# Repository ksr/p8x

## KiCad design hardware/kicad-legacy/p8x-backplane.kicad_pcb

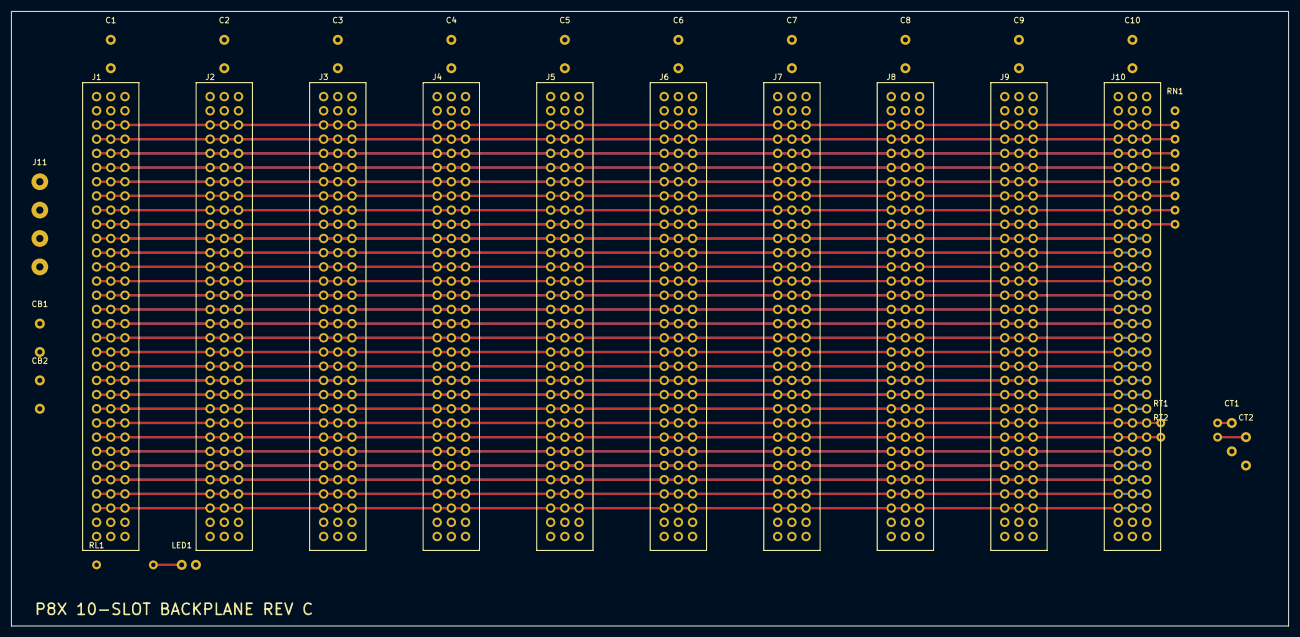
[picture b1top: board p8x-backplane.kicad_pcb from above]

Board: 4 copper layers, 228.6 x 110.0 mm, 30 parts (0 on the bottom side), 61 nets.

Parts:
C1, C2, C3, C4, C5, C6, C7, C8, C9, C10: C_DISC
CB1, CB2: CP_RADIAL
CT1, CT2: C_DISC
J1, J2, J3, J4, J5, J6, J7, J8, J9, J10: DIN96F
J11: TB4
LED1: LED5MM
RL1: R_AXIAL
RN1: SIP9
RT1, RT2: R_AXIAL

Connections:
A0: J1.C3, J2.C3, J3.C3, J4.C3, J5.C3, J6.C3, J7.C3, J8.C3, J9.C3, J10.C3
A1: J1.C4, J2.C4, J3.C4, J4.C4, J5.C4, J6.C4, J7.C4, J8.C4, J9.C4, J10.C4
A2: J1.C5, J2.C5, J3.C5, J4.C5, J5.C5, J6.C5, J7.C5, J8.C5, J9.C5, J10.C5
A3: J1.C6, J2.C6, J3.C6, J4.C6, J5.C6, J6.C6, J7.C6, J8.C6, J9.C6, J10.C6
A4: J1.C7, J2.C7, J3.C7, J4.C7, J5.C7, J6.C7, J7.C7, J8.C7, J9.C7, J10.C7
A5: J1.C8, J2.C8, J3.C8, J4.C8, J5.C8, J6.C8, J7.C8, J8.C8, J9.C8, J10.C8
A6: J1.C9, J2.C9, J3.C9, J4.C9, J5.C9, J6.C9, J7.C9, J8.C9, J9.C9, J10.C9
A7: J1.C10, J2.C10, J3.C10, J4.C10, J5.C10, J6.C10, J7.C10, J8.C10, J9.C10, J10.C10
A8: J1.C11, J2.C11, J3.C11, J4.C11, J5.C11, J6.C11, J7.C11, J8.C11, J9.C11, J10.C11
A9: J1.C12, J2.C12, J3.C12, J4.C12, J5.C12, J6.C12, J7.C12, J8.C12, J9.C12, J10.C12
A10: J1.C13, J2.C13, J3.C13, J4.C13, J5.C13, J6.C13, J7.C13, J8.C13, J9.C13, J10.C13
A11: J1.C14, J2.C14, J3.C14, J4.C14, J5.C14, J6.C14, J7.C14, J8.C14, J9.C14, J10.C14
A12: J1.C15, J2.C15, J3.C15, J4.C15, J5.C15, J6.C15, J7.C15, J8.C15, J9.C15, J10.C15
A13: J1.C16, J2.C16, J3.C16, J4.C16, J5.C16, J6.C16, J7.C16, J8.C16, J9.C16, J10.C16
A14: J1.C17, J2.C17, J3.C17, J4.C17, J5.C17, J6.C17, J7.C17, J8.C17, J9.C17, J10.C17
A15: J1.C18, J2.C18, J3.C18, J4.C18, J5.C18, J6.C18, J7.C18, J8.C18, J9.C18, J10.C18
ALUM: J1.C23, J2.C23, J3.C23, J4.C23, J5.C23, J6.C23, J7.C23, J8.C23, J9.C23, J10.C23
ALUS0: J1.C19, J2.C19, J3.C19, J4.C19, J5.C19, J6.C19, J7.C19, J8.C19, J9.C19, J10.C19
ALUS1: J1.C20, J2.C20, J3.C20, J4.C20, J5.C20, J6.C20, J7.C20, J8.C20, J9.C20, J10.C20
ALUS2: J1.C21, J2.C21, J3.C21, J4.C21, J5.C21, J6.C21, J7.C21, J8.C21, J9.C21, J10.C21
ALUS3: J1.C22, J2.C22, J3.C22, J4.C22, J5.C22, J6.C22, J7.C22, J8.C22, J9.C22, J10.C22
CIN: J1.C24, J2.C24, J3.C24, J4.C24, J5.C24, J6.C24, J7.C24, J8.C24, J9.C24, J10.C24
CLK: J1.A24, J2.A24, J3.A24, J4.A24, J5.A24, J6.A24, J7.A24, J8.A24, J9.A24, J10.A24, RT1.1
CLKB: J1.A25, J2.A25, J3.A25, J4.A25, J5.A25, J6.A25, J7.A25, J8.A25, J9.A25, J10.A25, RT2.1
CLKB_T: CT2.1, RT2.2
CLK_T: CT1.1, RT1.2
D0: J1.A3, J2.A3, J3.A3, J4.A3, J5.A3, J6.A3, J7.A3, J8.A3, J9.A3, J10.A3, RN1.2
D1: J1.A4, J2.A4, J3.A4, J4.A4, J5.A4, J6.A4, J7.A4, J8.A4, J9.A4, J10.A4, RN1.3
D2: J1.A5, J2.A5, J3.A5, J4.A5, J5.A5, J6.A5, J7.A5, J8.A5, J9.A5, J10.A5, RN1.4
D3: J1.A6, J2.A6, J3.A6, J4.A6, J5.A6, J6.A6, J7.A6, J8.A6, J9.A6, J10.A6, RN1.5
D4: J1.A7, J2.A7, J3.A7, J4.A7, J5.A7, J6.A7, J7.A7, J8.A7, J9.A7, J10.A7, RN1.6
D5: J1.A8, J2.A8, J3.A8, J4.A8, J5.A8, J6.A8, J7.A8, J8.A8, J9.A8, J10.A8, RN1.7
D6: J1.A9, J2.A9, J3.A9, J4.A9, J5.A9, J6.A9, J7.A9, J8.A9, J9.A9, J10.A9, RN1.8
D7: J1.A10, J2.A10, J3.A10, J4.A10, J5.A10, J6.A10, J7.A10, J8.A10, J9.A10, J10.A10, RN1.9
DLD0: J1.A16, J2.A16, J3.A16, J4.A16, J5.A16, J6.A16, J7.A16, J8.A16, J9.A16, J10.A16
DLD1: J1.A17, J2.A17, J3.A17, J4.A17, J5.A17, J6.A17, J7.A17, J8.A17, J9.A17, J10.A17
DLD2: J1.A18, J2.A18, J3.A18, J4.A18, J5.A18, J6.A18, J7.A18, J8.A18, J9.A18, J10.A18
DLD3: J1.A19, J2.A19, J3.A19, J4.A19, J5.A19, J6.A19, J7.A19, J8.A19, J9.A19, J10.A19
DOE0: J1.A12, J2.A12, J3.A12, J4.A12, J5.A12, J6.A12, J7.A12, J8.A12, J9.A12, J10.A12
DOE1: J1.A13, J2.A13, J3.A13, J4.A13, J5.A13, J6.A13, J7.A13, J8.A13, J9.A13, J10.A13
DOE2: J1.A14, J2.A14, J3.A14, J4.A14, J5.A14, J6.A14, J7.A14, J8.A14, J9.A14, J10.A14
DOE3: J1.A15, J2.A15, J3.A15, J4.A15, J5.A15, J6.A15, J7.A15, J8.A15, J9.A15, J10.A15
GND: C1.2, C2.2, C3.2, C4.2, C5.2, C6.2, C7.2, C8.2, C9.2, C10.2, CB1.2, CB2.2, CT1.2, CT2.2, J1.A31, J1.A32, J1.B3, J1.B4, J1.B5, J1.B6, J1.B7, J1.B8, J1.B9, J1.B10, J1.B11, J1.B12, J1.B13, J1.B14, J1.B15, J1.B16, J1.B17, J1.B18, J1.B19, J1.B20, J1.B21, J1.B22, J1.B23, J1.B24, J1.B25, J1.B26, J1.B27, J1.B28, J1.B29, J1.B30, J1.B31, J1.B32, J1.C31, J1.C32, J2.A31, J2.A32, J2.B3, J2.B4, J2.B5, J2.B6, J2.B7, J2.B8, J2.B9, J2.B10, J2.B11, J2.B12, J2.B13, J2.B14, J2.B15, J2.B16, J2.B17, J2.B18, J2.B19, J2.B20, J2.B21, J2.B22, J2.B23, J2.B24, J2.B25, J2.B26, J2.B27, J2.B28, J2.B29, J2.B30, J2.B31, J2.B32, J2.C31, J2.C32, J3.A31, J3.A32, J3.B3, J3.B4, J3.B5, J3.B6, J3.B7, J3.B8, J3.B9, J3.B10, J3.B11, J3.B12, J3.B13, J3.B14, J3.B15, J3.B16, J3.B17, J3.B18, J3.B19, J3.B20, J3.B21, J3.B22, J3.B23, J3.B24, J3.B25, J3.B26, J3.B27, J3.B28, J3.B29, J3.B30, J3.B31, J3.B32, J3.C31, J3.C32, J4.A31, J4.A32, J4.B3, J4.B4, J4.B5, J4.B6, J4.B7, J4.B8, J4.B9, J4.B10, J4.B11, J4.B12, J4.B13, J4.B14, J4.B15, J4.B16, J4.B17, J4.B18, J4.B19, J4.B20, J4.B21, J4.B22, J4.B23, J4.B24, J4.B25, J4.B26, J4.B27, J4.B28, J4.B29, J4.B30, J4.B31, J4.B32, J4.C31, J4.C32, J5.A31, J5.A32, J5.B3, J5.B4, J5.B5, J5.B6, J5.B7, J5.B8, J5.B9, J5.B10, J5.B11, J5.B12, J5.B13, J5.B14, J5.B15, J5.B16, J5.B17, J5.B18, J5.B19, J5.B20, J5.B21, J5.B22, J5.B23, J5.B24, J5.B25, J5.B26, J5.B27, J5.B28, J5.B29, J5.B30, J5.B31, J5.B32, J5.C31, J5.C32, J6.A31, J6.A32, J6.B3, J6.B4, J6.B5, J6.B6, J6.B7, J6.B8, J6.B9, J6.B10, J6.B11, J6.B12, J6.B13, J6.B14, J6.B15, J6.B16, J6.B17, J6.B18, J6.B19, J6.B20, J6.B21, J6.B22, J6.B23, J6.B24, J6.B25, J6.B26, J6.B27, J6.B28, J6.B29, J6.B30, J6.B31, J6.B32, J6.C31, J6.C32, J7.A31, J7.A32, J7.B3, J7.B4, J7.B5, J7.B6, J7.B7, J7.B8, J7.B9, J7.B10, J7.B11, J7.B12, J7.B13, J7.B14, J7.B15, J7.B16, J7.B17, J7.B18, J7.B19, J7.B20, J7.B21, J7.B22, J7.B23, J7.B24, J7.B25, J7.B26, J7.B27, J7.B28, J7.B29, J7.B30, J7.B31, J7.B32, J7.C31, J7.C32, J8.A31, J8.A32, J8.B3, J8.B4, J8.B5, J8.B6, J8.B7, J8.B8, J8.B9, J8.B10, J8.B11, J8.B12, J8.B13, J8.B14, J8.B15, J8.B16, J8.B17, J8.B18, J8.B19, J8.B20, J8.B21, J8.B22, J8.B23, J8.B24, J8.B25, J8.B26, J8.B27, J8.B28, J8.B29, J8.B30, J8.B31, J8.B32, J8.C31, J8.C32, J9.A31, J9.A32, J9.B3, J9.B4, J9.B5, J9.B6, J9.B7, J9.B8, J9.B9, J9.B10, J9.B11, J9.B12, J9.B13, J9.B14, J9.B15, J9.B16, J9.B17, J9.B18, J9.B19, J9.B20, J9.B21, J9.B22, J9.B23, J9.B24, J9.B25, J9.B26, J9.B27, J9.B28, J9.B29, J9.B30, J9.B31, J9.B32, J9.C31, J9.C32, J10.A31, J10.A32, J10.B3, J10.B4, J10.B5, J10.B6, J10.B7, J10.B8, J10.B9, J10.B10, J10.B11, J10.B12, J10.B13, J10.B14, J10.B15, J10.B16, J10.B17, J10.B18, J10.B19, J10.B20, J10.B21, J10.B22, J10.B23, J10.B24, J10.B25, J10.B26, J10.B27, J10.B28, J10.B29, J10.B30, J10.B31, J10.B32, J10.C31, J10.C32, J11.3, J11.4, LED1.1
LDF: J1.A26, J2.A26, J3.A26, J4.A26, J5.A26, J6.A26, J7.A26, J8.A26, J9.A26, J10.A26
LED_A: LED1.2, RL1.2
PDEC: J1.A23, J2.A23, J3.A23, J4.A23, J5.A23, J6.A23, J7.A23, J8.A23, J9.A23, J10.A23
PINC: J1.A22, J2.A22, J3.A22, J4.A22, J5.A22, J6.A22, J7.A22, J8.A22, J9.A22, J10.A22
PSEL0: J1.A20, J2.A20, J3.A20, J4.A20, J5.A20, J6.A20, J7.A20, J8.A20, J9.A20, J10.A20
PSEL1: J1.A21, J2.A21, J3.A21, J4.A21, J5.A21, J6.A21, J7.A21, J8.A21, J9.A21, J10.A21
RES_N: J1.A11, J2.A11, J3.A11, J4.A11, J5.A11, J6.A11, J7.A11, J8.A11, J9.A11, J10.A11
SH0: J1.C25, J2.C25, J3.C25, J4.C25, J5.C25, J6.C25, J7.C25, J8.C25, J9.C25, J10.C25
SH1: J1.C26, J2.C26, J3.C26, J4.C26, J5.C26, J6.C26, J7.C26, J8.C26, J9.C26, J10.C26
SPARE0: J1.A27, J2.A27, J3.A27, J4.A27, J5.A27, J6.A27, J7.A27, J8.A27, J9.A27, J10.A27
SPARE1: J1.A28, J2.A28, J3.A28, J4.A28, J5.A28, J6.A28, J7.A28, J8.A28, J9.A28, J10.A28
SPARE2: J1.A29, J2.A29, J3.A29, J4.A29, J5.A29, J6.A29, J7.A29, J8.A29, J9.A29, J10.A29
SPARE3: J1.A30, J2.A30, J3.A30, J4.A30, J5.A30, J6.A30, J7.A30, J8.A30, J9.A30, J10.A30
SPARE4: J1.C27, J2.C27, J3.C27, J4.C27, J5.C27, J6.C27, J7.C27, J8.C27, J9.C27, J10.C27
SPARE5: J1.C28, J2.C28, J3.C28, J4.C28, J5.C28, J6.C28, J7.C28, J8.C28, J9.C28, J10.C28
SPARE6: J1.C29, J2.C29, J3.C29, J4.C29, J5.C29, J6.C29, J7.C29, J8.C29, J9.C29, J10.C29
SPARE7: J1.C30, J2.C30, J3.C30, J4.C30, J5.C30, J6.C30, J7.C30, J8.C30, J9.C30, J10.C30
VCC: C1.1, C2.1, C3.1, C4.1, C5.1, C6.1, C7.1, C8.1, C9.1, C10.1, CB1.1, CB2.1, J1.A1, J1.A2, J1.B1, J1.B2, J1.C1, J1.C2, J2.A1, J2.A2, J2.B1, J2.B2, J2.C1, J2.C2, J3.A1, J3.A2, J3.B1, J3.B2, J3.C1, J3.C2, J4.A1, J4.A2, J4.B1, J4.B2, J4.C1, J4.C2, J5.A1, J5.A2, J5.B1, J5.B2, J5.C1, J5.C2, J6.A1, J6.A2, J6.B1, J6.B2, J6.C1, J6.C2, J7.A1, J7.A2, J7.B1, J7.B2, J7.C1, J7.C2, J8.A1, J8.A2, J8.B1, J8.B2, J8.C1, J8.C2, J9.A1, J9.A2, J9.B1, J9.B2, J9.C1, J9.C2, J10.A1, J10.A2, J10.B1, J10.B2, J10.C1, J10.C2, J11.1, J11.2, RL1.1, RN1.1

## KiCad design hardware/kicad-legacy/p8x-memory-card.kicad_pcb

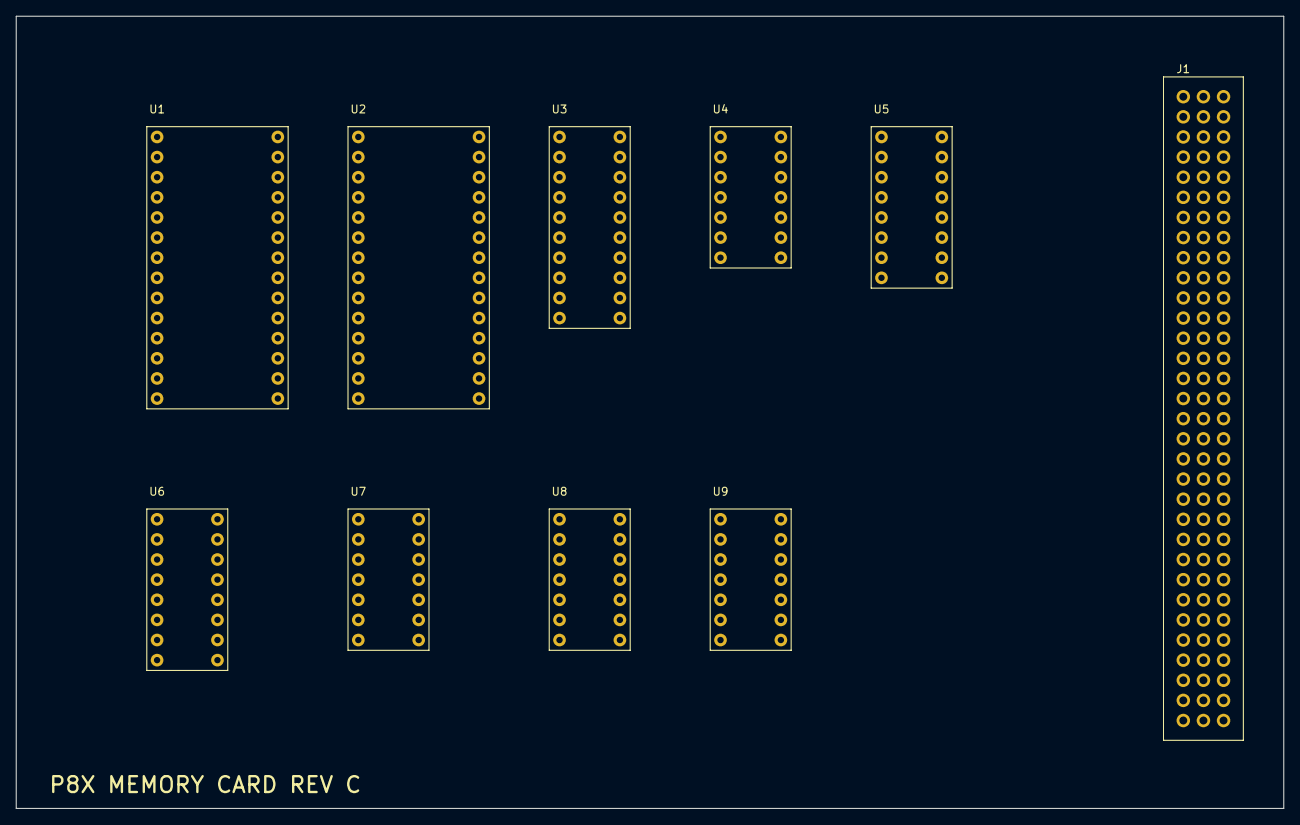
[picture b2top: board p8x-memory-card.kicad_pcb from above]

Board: 4 copper layers, 160.0 x 100.0 mm, 10 parts (0 on the bottom side), 49 nets, no tracks yet.

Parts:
J1: DIN96M_RA
U1, U2: DIP28W
U3: DIP20
U4, U7, U8, U9: DIP14
U5, U6: DIP16

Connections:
A0: J1.C3, U1.10, U2.10
A1: J1.C4, U1.9, U2.9
A2: J1.C5, U1.8, U2.8
A3: J1.C6, U1.7, U2.7
A4: J1.C7, U1.6, U2.6
A5: J1.C8, U1.5, U2.5
A6: J1.C9, U1.4, U2.4
A7: J1.C10, U1.3, U2.3
A8: J1.C11, U1.25, U2.25, U4.1
A9: J1.C12, U1.24, U2.24, U4.2
A10: J1.C13, U1.21, U2.21, U4.3
A11: J1.C14, U1.23, U2.23, U4.4
A12: J1.C15, U1.2, U2.2, U4.5
A13: J1.C16, U1.26, U2.26, U4.6
A14: J1.C17, U1.1, U2.1, U4.11
A15: J1.C18, U1.20, U4.12, U7.1
BOE_N: U3.19, U9.3
CLK: J1.A24, U8.2
D0: J1.A3, U3.2
D1: J1.A4, U3.3
D2: J1.A5, U3.4
D3: J1.A6, U3.5
D4: J1.A7, U3.6
D5: J1.A8, U3.7
D6: J1.A9, U3.8
D7: J1.A10, U3.9
DLD0: J1.A16, U6.1
DLD1: J1.A17, U6.2
DLD2: J1.A18, U6.3
DLD3: J1.A19, U6.4
DOE0: J1.A12, U5.1
DOE1: J1.A13, U5.2
DOE2: J1.A14, U5.3
DOE3: J1.A15, U5.4
GND: J1.A31, J1.A32, J1.B3, J1.B4, J1.B5, J1.B6, J1.B7, J1.B8, J1.B9, J1.B10, J1.B11, J1.B12, J1.B13, J1.B14, J1.B15, J1.B16, J1.B17, J1.B18, J1.B19, J1.B20, J1.B21, J1.B22, J1.B23, J1.B24, J1.B25, J1.B26, J1.B27, J1.B28, J1.B29, J1.B30, J1.B31, J1.B32, J1.C31, J1.C32, U1.14, U2.14, U3.10, U4.7, U5.5, U5.8, U6.5, U6.8, U7.4, U7.5, U7.7, U7.9, U7.10, U7.12, U7.13, U8.4, U8.5, U8.7, U8.9, U8.10, U8.12, U8.13, U9.4, U9.5, U9.7, U9.9, U9.10, U9.12, U9.13
IOPG_N: U4.8, U7.2
MD0: U1.11, U2.11, U3.18
MD1: U1.12, U2.12, U3.17
MD2: U1.13, U2.13, U3.16
MD3: U1.15, U2.15, U3.15
MD4: U1.16, U2.16, U3.14
MD5: U1.17, U2.17, U3.13
MD6: U1.18, U2.18, U3.12
MD7: U1.19, U2.19, U3.11
MEMW_N: U6.7, U8.1, U9.2
RAMCE_N: U2.20, U7.3
RD_N: U1.22, U2.22, U3.1, U5.7, U9.1
VCC: J1.A1, J1.A2, J1.B1, J1.B2, J1.C1, J1.C2, U1.28, U2.28, U3.20, U4.14, U5.6, U5.16, U6.6, U6.16, U7.14, U8.14, U9.14
WE_N: U1.27, U2.27, U8.3

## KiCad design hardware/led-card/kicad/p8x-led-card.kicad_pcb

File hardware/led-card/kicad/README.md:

# led-card -- KiCad

Generated by `generators/gen_kicad.py` from the canonical gen_eagle netlist
(`CARDS["led-card"]`), same standard as the memory card: 4-layer (F/B signals,
In1=GND, In2=VCC planes), a bypass cap above each IC, a labelled LED/jumper bank,
part values on silk. Routed with Freerouting. GENERATORS ARE CANON -- edit
`gen_kicad.py` and re-run `generators/build_kicad_card.sh led-card`.

| File | What |
|------|------|
| `p8x-led-card.kicad_pcb` | the board |
| `p8x-led-card.ses` | the Freerouting routing |
| `p8x-led-card-gerbers.zip` | orderable gerbers |
| `p8x-led-card-placement.pdf` | parts placement (refs+values) |
| `p8x-led-card-render-top.png` / `-3d.png` | renders |

Exotic parts use the closest standard KiCad footprint (flagged when built).

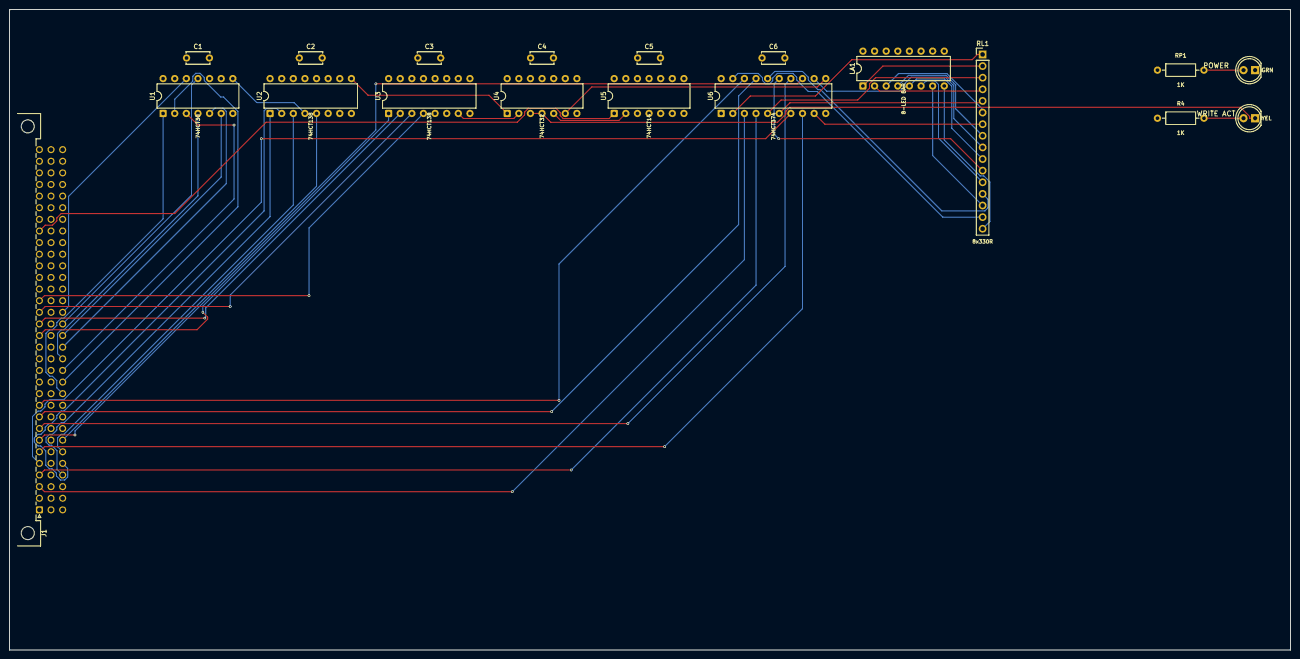
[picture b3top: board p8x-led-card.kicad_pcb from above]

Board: 4 copper layers, 280.0 x 140.0 mm, 19 parts (0 on the bottom side), 51 nets.

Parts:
C1, C2, C3, C4, C5, C6: 100nF; C_Disc_D5.0mm_W2.5mm_P5.00mm
J1: MABC96R; DIN41612_C_3x32_Male_Horizontal_THT
LA1: 8-LED BAR; DIP-16_W7.62mm
LED3: GRN; LED_D5.0mm
LED4: YEL; LED_D5.0mm
R4: 1K; R_Axial_DIN0207_L6.3mm_D2.5mm_P10.16mm_Horizontal
RL1: 8x330R; PinHeader_1x16_P2.54mm_Vertical
RP1: 1K; R_Axial_DIN0207_L6.3mm_D2.5mm_P10.16mm_Horizontal
U1: 74HCT30; DIP-14_W7.62mm
U2, U3: 74HCT138; DIP-16_W7.62mm
U4: 74HCT32; DIP-14_W7.62mm
U5: 74HCT14; DIP-14_W7.62mm
U6: 74HCT374; DIP-20_W7.62mm

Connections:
-MEMW: U3.7, U4.2
-SEL: U2.9, U4.1
A1: J1.c4, U2.1
A2: J1.c5, U2.2
A3: J1.c6, U2.3
A4: J1.c7, U2.5
A8: J1.c11, U1.1
A9: J1.c12, U1.2
A10: J1.c13, U1.3
A11: J1.c14, U1.4
A12: J1.c15, U1.5
A13: J1.c16, U1.6
A14: J1.c17, U1.11
A15: J1.c18, U1.12
CLKB: J1.a25, U5.1
CLKBN: U4.5, U5.2
D0: J1.a3, U6.3
D1: J1.a4, U6.4
D2: J1.a5, U6.7
D3: J1.a6, U6.8
D4: J1.a7, U6.13
D5: J1.a8, U6.14
D6: J1.a9, U6.17
D7: J1.a10, U6.18
DLD0: J1.a16, U3.1
DLD1: J1.a17, U3.2
DLD2: J1.a18, U3.3
DLD3: J1.a19, U3.4
GND: C1.2, C2.2, C3.2, C4.2, C5.2, C6.2, J1.a31, J1.a32, J1.b3, J1.b5, J1.b7, J1.b9, J1.b11, J1.b13, J1.b15, J1.b17, J1.b19, J1.b21, J1.b23, J1.b25, J1.b31, J1.b32, J1.c31, J1.c32, LA1.9, LA1.10, LA1.11, LA1.12, LA1.13, LA1.14, LA1.15, LA1.16, LED3.1, U1.7, U2.8, U3.5, U3.8, U4.7, U4.9, U4.10, U4.12, U4.13, U5.3, U5.5, U5.7, U5.9, U5.11, U5.13, U6.1, U6.10
IOPG: U1.8, U2.4
LCK: U4.6, U6.11
LEDP: LED3.2, RP1.2
LEDWR: LED4.2, R4.2
LP0: RL1.1, U6.2
LP1: RL1.3, U6.5
LP2: RL1.5, U6.6
LP3: RL1.7, U6.9
LP4: RL1.9, U6.12
LP5: RL1.11, U6.15
LP6: RL1.13, U6.16
LP7: RL1.15, U6.19
LR0: LA1.1, RL1.2
LR1: LA1.2, RL1.4
LR2: LA1.3, RL1.6
LR3: LA1.4, RL1.8
LR4: LA1.5, RL1.10
LR5: LA1.6, RL1.12
LR6: LA1.7, RL1.14
LR7: LA1.8, RL1.16
VCC: C1.1, C2.1, C3.1, C4.1, C5.1, C6.1, J1.a1, J1.a2, J1.b1, J1.b2, J1.c1, J1.c2, R4.1, RP1.1, U1.14, U2.6, U2.16, U3.6, U3.16, U4.14, U5.14, U6.20
WRSEL: LED4.1, U4.3, U4.4

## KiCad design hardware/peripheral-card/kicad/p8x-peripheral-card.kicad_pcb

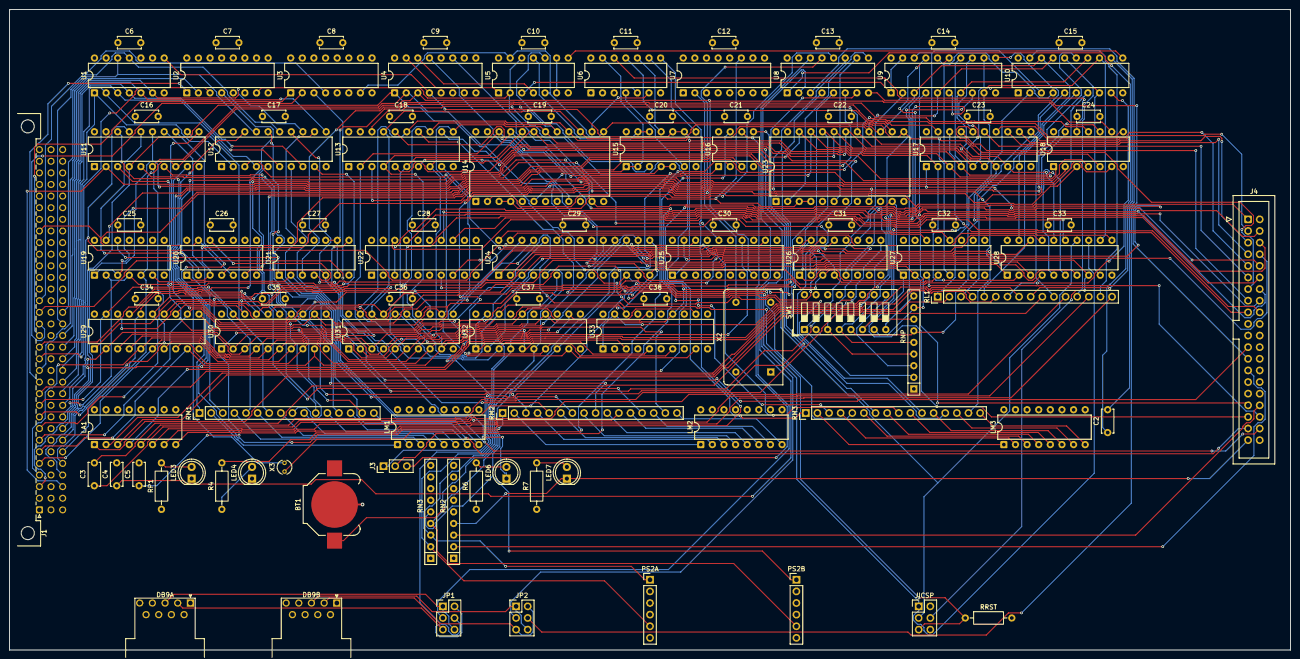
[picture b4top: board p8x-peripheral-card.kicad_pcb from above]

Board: 4 copper layers, 280.0 x 140.0 mm, 104 parts (0 on the bottom side), 214 nets.

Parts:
BT1: CR2032; BatteryHolder_Keystone_3000_1x12mm
C2, C3, C4, C5: 1uF; C_Disc_D5.0mm_W2.5mm_P5.00mm
C6, C7, C8, C9, C10, C11, C12, C13, C14, C15, C16, C17, C18, C19, C20, C21, C22, C23, C24, C25, C26, C27, C28, C29, C30, C31, C32, C33, C34, C35, C36, C37, C38: 100nF; C_Disc_D5.0mm_W2.5mm_P5.00mm
DB9A: SERIAL1; DSUB-9_Socket_Horizontal_P2.77x2.54mm_EdgePinOffset9.40mm
DB9B: SERIAL2; DSUB-9_Socket_Horizontal_P2.77x2.54mm_EdgePinOffset9.40mm
J1: MABC96R; DIN41612_C_3x32_Male_Horizontal_THT
J3: 1x3; PinHeader_1x03_P2.54mm_Vertical
J4: IDE-40; IDC-Header_2x20_P2.54mm_Vertical
JICSP: ICSP; PinHeader_2x03_P2.54mm_Vertical
JP1: S1 SWAP; PinHeader_2x03_P2.54mm_Vertical
JP2: S2 SWAP; PinHeader_2x03_P2.54mm_Vertical
LA1: 8-LED BAR; DIP-16_W7.62mm
LED3, LED7: GRN; LED_D5.0mm
LED4, LED6: YEL; LED_D5.0mm
LM1: A0-7; DIP-16_W7.62mm
LM2: A8-15; DIP-16_W7.62mm
LM3: D0-7; DIP-16_W7.62mm
PS2A: PS2-KBD; PinHeader_1x06_P2.54mm_Vertical
PS2B: PS2-MOUSE; PinHeader_1x06_P2.54mm_Vertical
R4, R6: 1K; R_Axial_DIN0207_L6.3mm_D2.5mm_P10.16mm_Horizontal
R7: 330R; R_Axial_DIN0207_L6.3mm_D2.5mm_P10.16mm_Horizontal
RL1: 8X330R; PinHeader_1x16_P2.54mm_Vertical
RM1, RM2, RM3: 8X330R; PinHeader_1x16_P2.54mm_Vertical
RN2: 8X10K; R_Array_SIP9
RN3: 4X10K; R_Array_SIP9
RNP: 8X10K; R_Array_SIP9
RP1: 1K; R_Axial_DIN0207_L6.3mm_D2.5mm_P10.16mm_Horizontal
RRST: 10K; R_Axial_DIN0207_L6.3mm_D2.5mm_P10.16mm_Horizontal
SW1: INPUT; SW_DIP_SPSTx08_Slide_9.78x22.5mm_W7.62mm_P2.54mm
U1: 74HCT30; DIP-14_W7.62mm
U2, U3, U4, U26, U27: 74HCT138; DIP-16_W7.62mm
U5: 74HCT32; DIP-14_W7.62mm
U6, U21: 74HCT08; DIP-14_W7.62mm
U7: 74HCT161; DIP-16_W7.62mm
U8: MAX232; DIP-16_W7.62mm
U9, U11, U12, U13, U32, U33: 74HCT244; DIP-20_W7.62mm
U10, U22, U28, U29, U30, U31: 74HCT374; DIP-20_W7.62mm
U14, U23: 6850; DIP-24_W15.24mm
U15: 74HCT00; DIP-14_W7.62mm
U16: DS1302; DIP-8_W7.62mm
U17: 74HCT245; DIP-20_W7.62mm
U18: 74HCT14; DIP-14_W7.62mm
U19, U20: 74HCT10; DIP-14_W7.62mm
U24: PS/2 MCU; DIP-28_W7.62mm
U25: WIN CMP; DIP-20_W7.62mm
X2: 2.4576MHZ; Oscillator_DIP-14
X3: 32.768KHZ; Crystal_Round_D3.0mm_Vertical

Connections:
-CFOE: U17.19, U21.6, U21.9, U21.10
-CFSEL: U18.11, U21.3
-CS0: J4.37, U19.12, U21.1
-CS1: J4.38, U19.6, U21.2
-DASP: J4.39, LED7.1, RN2.4
-IOR: J4.25, U17.1, U20.12, U21.4
-IOW: J4.23, U20.6, U21.5
-MEMW: U3.7, U5.5, U5.13, U14.13, U18.5, U23.13, U27.5
-P0: U4.15, U5.1
-P1: U4.14, U5.4
-P2: U4.13, U14.9, U15.4, U15.5
-P4: U4.11, U18.13, U23.9
-PDIAG: J4.34, RN2.3
-PSSEL: U25.19, U26.4, U27.4
-RD: U2.7, U5.2, U5.12, U18.3, U26.5
-RES: J1.a11, J4.1
-RESET: JICSP.5, RRST.1, U24.1
-RR0: U24.2, U26.15, U28.1
-RR1: U26.14, U29.1
-RR2: U24.3, U26.13, U30.1
-RR3: U26.12, U31.1
-RR4: U26.11, U32.1, U32.19
-RR6: U26.9, U33.1, U33.19
-SWOE: U5.3, U9.1, U9.19
-WR1: U24.27, U27.14
-WR3: U24.28, U27.12
A0: J1.c3, J4.35, U11.2, U14.11, U23.11, U26.1, U27.1
A1: J1.c4, J4.33, U4.1, U11.4, U26.2, U27.2
A2: J1.c5, J4.36, U4.2, U11.6, U26.3, U27.3
A3: J1.c6, U4.3, U11.8, U18.9, U19.5, U25.8
A3N: U18.8, U19.13
A4: J1.c7, U11.11, U19.2, U19.4, U25.12
A5: J1.c8, U11.13, U25.14
A6: J1.c9, U11.15, U25.16
A7: J1.c10, U11.17, U25.18
A8: J1.c11, U1.1, U12.2
A9: J1.c12, U1.2, U12.4
A10: J1.c13, U1.3, U12.6
A11: J1.c14, U1.4, U12.8
A12: J1.c15, U1.5, U12.11
A13: J1.c16, U1.6, U12.13
A14: J1.c17, U1.11, U12.15
A15: J1.c18, U1.12, U12.17
ACCP: U6.10, U15.11
ACTK: LED6.1, U21.8
BCLK: U7.11, U14.3, U14.4, U23.3, U23.4
BOEISH: U5.11, U15.12, U15.13
BOSC: U7.2, X2.8
C1MN: C2.2, U8.3
C1PN: C2.1, U8.1
C2MN: C3.2, U8.5
C2PN: C3.1, U8.4
CFD0: J4.17, U17.18
CFD1: J4.15, U17.17
CFD2: J4.13, U17.16
CFD3: J4.11, U17.15
CFD4: J4.9, U17.14
CFD5: J4.7, U17.13
CFD6: J4.5, U17.12
CFD7: J4.3, U17.11
CFD8: J4.4, U22.3
CFD9: J4.6, U22.4
CFD10: J4.8, U22.7
CFD11: J4.10, U22.8
CFD12: J4.12, U22.13
CFD13: J4.14, U22.14
CFD14: J4.16, U22.17
CFD15: J4.18, U22.18
CFSELP: U18.10, U20.1, U20.3
CLKB: J1.a25, U6.5, U6.13, U15.1, U15.2, U20.5, U20.13
CLKBN: U5.10, U15.3
D0: J1.a3, U9.18, U10.3, U13.2, U14.22, U17.2, U23.22, U28.2, U29.2, U30.2, U31.2, U32.18, U33.18
D1: J1.a4, U9.16, U10.4, U13.4, U14.21, U17.3, U23.21, U28.5, U29.5, U30.5, U31.5, U32.16, U33.16
D2: J1.a5, U9.14, U10.7, U13.6, U14.20, U17.4, U23.20, U28.6, U29.6, U30.6, U31.6, U32.14, U33.14
D3: J1.a6, U9.12, U10.8, U13.8, U14.19, U17.5, U23.19, U28.9, U29.9, U30.9, U31.9, U32.12, U33.12
D4: J1.a7, U9.9, U10.13, U13.11, U14.18, U17.6, U23.18, U28.12, U29.12, U30.12, U31.12, U32.9, U33.9
D5: J1.a8, U9.7, U10.14, U13.13, U14.17, U17.7, U23.17, U28.15, U29.15, U30.15, U31.15, U32.7, U33.7
D6: J1.a9, U9.5, U10.17, U13.15, U14.16, U17.8, U23.16, U28.16, U29.16, U30.16, U31.16, U32.5, U33.5
D7: J1.a10, U9.3, U10.18, U13.17, U14.15, U17.9, U23.15, U28.19, U29.19, U30.19, U31.19, U32.3, U33.3
DLD0: J1.a16, U3.1
DLD1: J1.a17, U3.2
DLD2: J1.a18, U3.3
DLD3: J1.a19, U3.4
DOE0: J1.a12, U2.1
DOE1: J1.a13, U2.2
DOE2: J1.a14, U2.3
DOE3: J1.a15, U2.4
E2: U6.11, U23.14
EEN: U6.6, U14.14
GND: BT1.2, C4.2, C5.2, C6.2, C7.2, C8.2, C9.2, C10.2, C11.2, C12.2, C13.2, C14.2, C15.2, C16.2, C17.2, C18.2, C19.2, C20.2, C21.2, C22.2, C23.2, C24.2, C25.2, C26.2, C27.2, C28.2, C29.2, C30.2, C31.2, C32.2, C33.2, C34.2, C35.2, C36.2, C37.2, C38.2, DB9A.5, DB9B.5, J1.a31, J1.a32, J1.b3, J1.b5, J1.b7, J1.b9, J1.b11, J1.b13, J1.b15, J1.b17, J1.b19, J1.b21, J1.b23, J1.b25, J1.b31, J1.b32, J1.c31, J1.c32, J4.2, J4.19, J4.22, J4.24, J4.26, J4.28, J4.30, J4.40, JICSP.6, LA1.9, LA1.10, LA1.11, LA1.12, LA1.13, LA1.14, LA1.15, LA1.16, LED3.1, LED4.1, LM1.9, LM1.10, LM1.11, LM1.12, LM1.13, LM1.14, LM1.15, LM1.16, LM2.9, LM2.10, LM2.11, LM2.12, LM2.13, LM2.14, LM2.15, LM2.16, LM3.9, LM3.10, LM3.11, LM3.12, LM3.13, LM3.14, LM3.15, LM3.16, PS2A.3, PS2B.3, SW1.9, SW1.10, SW1.11, SW1.12, SW1.13, SW1.14, SW1.15, SW1.16, U1.7, U2.5, U2.8, U3.5, U3.8, U4.5, U4.8, U5.7, U6.1, U6.2, U6.7, U7.3, U7.4, U7.5, U7.6, U7.8, U8.15, U9.10, U10.1, U10.10, U11.1, U11.10, U11.19, U12.1, U12.10, U12.19, U13.1, U13.10, U13.19, U14.1, U14.23, U14.24, U15.7, U16.4, U17.10, U18.7, U19.7, U19.9, U19.10, U19.11, U20.7, U20.9, U20.10, U20.11, U21.7, U21.12, U21.13, U22.10, U22.11, U23.1, U23.23, U23.24, U24.8, U24.22, U25.2, U25.3, U25.4, U25.5, U25.6, U25.7, U25.10, U25.13, U25.17, U26.8, U27.8, U28.10, U29.10, U30.10, U31.10, U32.10, U32.11, U32.13, U32.15, U32.17, U33.6, U33.10, U33.11, U33.13, U33.17, X2.7
IOPG: U1.8, U4.4, U15.9, U15.10, U18.1, U25.1
IOPGN: U6.9, U15.8
IOPGP: U18.2, U19.1, U19.3
IORDY: J4.27, RN2.2
LCK: U5.8, U10.11
LDA: U24.23, U28.11
LDB: U24.25, U30.11
LDSA: U24.24, U29.11
LDSB: U24.26, U31.11
LED4A: LED4.2, R4.1
LEDAC: LED6.2, R6.2
LEDDA: LED7.2, R7.2
LEDP: LED3.2, RP1.2
LP0: RL1.1, U10.2
LP1: RL1.3, U10.5
LP2: RL1.5, U10.6
LP3: RL1.7, U10.9
LP4: RL1.9, U10.12
LP5: RL1.11, U10.15
LP6: RL1.13, U10.16
LP7: RL1.15, U10.19
LR0: LA1.1, RL1.2
LR1: LA1.2, RL1.4
LR2: LA1.3, RL1.6
LR3: LA1.4, RL1.8
LR4: LA1.5, RL1.10
LR5: LA1.6, RL1.12
LR6: LA1.7, RL1.14
LR7: LA1.8, RL1.16
LW1: U5.6, U5.9
MA0: RM1.1, U11.18
MA1: RM1.3, U11.16
MA2: RM1.5, U11.14
MA3: RM1.7, U11.12
MA4: RM1.9, U11.9
MA5: RM1.11, U11.7
MA6: RM1.13, U11.5
MA7: RM1.15, U11.3
MA8: RM2.1, U12.18
MA9: RM2.3, U12.16
MA10: RM2.5, U12.14
MA11: RM2.7, U12.12
MA12: RM2.9, U12.9
MA13: RM2.11, U12.7
MA14: RM2.13, U12.5
MA15: RM2.15, U12.3
MB0: U24.14, U28.3, U29.3, U30.3, U31.3
MB1: U24.15, U28.4, U29.4, U30.4, U31.4
MB2: U24.16, U28.7, U29.7, U30.7, U31.7
MB3: JICSP.4, U24.17, U28.8, U29.8, U30.8, U31.8
MB4: JICSP.1, U24.18, U28.13, U29.13, U30.13, U31.13
MB5: JICSP.3, U24.19, U28.14, U29.14, U30.14, U31.14
MB6: U24.12, U28.17, U29.17, U30.17, U31.17
MB7: U24.13, U28.18, U29.18, U30.18, U31.18
MD0: RM3.1, U13.18
MD1: RM3.3, U13.16
MD2: RM3.5, U13.14
MD3: RM3.7, U13.12
MD4: RM3.9, U13.9
MD5: RM3.11, U13.7
MD6: RM3.13, U13.5
MD7: RM3.15, U13.3
ML0_0: LM1.1, RM1.2
ML0_1: LM1.2, RM1.4
ML0_2: LM1.3, RM1.6
ML0_3: LM1.4, RM1.8
ML0_4: LM1.5, RM1.10
ML0_5: LM1.6, RM1.12
ML0_6: LM1.7, RM1.14
ML0_7: LM1.8, RM1.16
ML1_0: LM2.1, RM2.2
ML1_1: LM2.2, RM2.4
ML1_2: LM2.3, RM2.6
ML1_3: LM2.4, RM2.8
ML1_4: LM2.5, RM2.10
ML1_5: LM2.6, RM2.12
ML1_6: LM2.7, RM2.14
ML1_7: LM2.8, RM2.16
ML2_0: LM3.1, RM3.2
ML2_1: LM3.2, RM3.4
ML2_2: LM3.3, RM3.6
ML2_3: LM3.4, RM3.8
ML2_4: LM3.5, RM3.10
ML2_5: LM3.6, RM3.12
ML2_6: LM3.7, RM3.14
ML2_7: LM3.8, RM3.16
P2P: U6.4, U15.6
P4P: U6.12, U18.12
PS2CKA: PS2A.5, RN3.2, U24.4, U32.2
PS2CKB: PS2B.5, RN3.4, U24.5, U32.6
PS2DA: PS2A.1, RN3.3, U24.6, U32.4
PS2DB: PS2B.1, RN3.5, U24.11, U32.8
RDP: U18.4, U20.2
RTCCE: J3.1, U16.5
RTCIO: J3.3, U16.6
RTCSCLK: J3.2, U16.7
RTCX1: U16.2, X3.1
RTCX2: U16.3, X3.2
RXD: U8.12, U14.2
RXD2: U8.9, U23.2
S1RXD: DB9A.2, JP1.2, JP1.5
S1TXD: DB9A.3, JP1.1, JP1.6
S2RXD: DB9B.2, JP2.2, JP2.5
S2TXD: DB9B.3, JP2.1, JP2.6
SELP: R4.2, U6.8
SIN: JP1.4, U8.13
SIN2: JP2.4, U8.8
SOUT: JP1.3, U8.14
SOUT2: JP2.3, U8.7
SWN0: RNP.2, SW1.1, U9.2
SWN1: RNP.3, SW1.2, U9.4
SWN2: RNP.4, SW1.3, U9.6
SWN3: RNP.5, SW1.4, U9.8
SWN4: RNP.6, SW1.5, U9.11
SWN5: RNP.7, SW1.6, U9.13
SWN6: RNP.8, SW1.7, U9.15
SWN7: RNP.9, SW1.8, U9.17
TXD: U8.11, U14.6
TXD2: U8.10, U23.6
VBAT: BT1.1, U16.1
VCC: C6.1, C7.1, C8.1, C9.1, C10.1, C11.1, C12.1, C13.1, C14.1, C15.1, C16.1, C17.1, C18.1, C19.1, C20.1, C21.1, C22.1, C23.1, C24.1, C25.1, C26.1, C27.1, C28.1, C29.1, C30.1, C31.1, C32.1, C33.1, C34.1, C35.1, C36.1, C37.1, C38.1, J1.a1, J1.a2, J1.b1, J1.b2, J1.c1, J1.c2, J4.29, JICSP.2, PS2A.4, PS2B.4, R6.1, R7.1, RN2.1, RN3.1, RNP.1, RP1.1, RRST.2, U1.14, U2.6, U2.16, U3.6, U3.16, U4.6, U4.16, U5.14, U6.14, U7.1, U7.7, U7.9, U7.10, U7.16, U8.16, U9.20, U10.20, U11.20, U12.20, U13.20, U14.8, U14.10, U14.12, U15.14, U16.8, U17.20, U18.14, U19.14, U20.14, U21.14, U22.1, U22.20, U23.8, U23.10, U23.12, U24.7, U24.20, U25.9, U25.11, U25.15, U25.20, U26.6, U26.16, U27.6, U27.16, U28.20, U29.20, U30.20, U31.20, U32.20, U33.2, U33.4, U33.8, U33.15, U33.20, X2.14
VMN: C5.1, U8.6
VPN: C4.1, U8.2
WRP: U18.6, U20.4

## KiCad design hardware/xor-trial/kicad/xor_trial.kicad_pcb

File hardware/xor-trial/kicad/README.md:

# XOR Trial Board — KiCad

The [XOR trial circuit](../README.md) realised as an orderable **KiCad 10** PCB,
generated by a script (generators are canon here too — edit `gen_xor.py`, re-run,
don't hand-edit the `.kicad_pcb`). 62 × 44 mm, 2-layer, all through-hole.

| File | What it is |
|------|-----------|
| `gen_sch.py` | the **schematic** generator — emits `xor_trial.kicad_sch` (symbols, wires, net labels, power symbols); written to pass ERC clean |
| `xor_trial.kicad_sch` | the generated schematic (open it in KiCad Eeschema) |
| `xor_trial_sch.pdf` | the schematic as a PDF |
| `gen_xor.py` | the **board** generator — builds the PCB with `pcbnew`: footprints, nets, routing, a bottom-layer GND pour, the Edge.Cuts outline, and `+`/`-` silk labels on the power header |
| `xor_trial.kicad_pcb` | the generated board (open it in KiCad Pcbnew) |
| `xor_trial.kicad_pro` | project file so it opens as a project |
| `xor_trial_gerbers.zip` | **the orderable output** — Gerbers + Excellon drill |

Two generators, one circuit: `gen_sch.py` builds the schematic and `gen_xor.py`
builds the board, and they hand-code the **same netlist** independently (this
tiny board is not big enough to justify a full schematic-driven-layout netlist
import). The schematic passes ERC and the board passes DRC, both clean.

## Regenerate

The **schematic** generator runs under the *system* python3 (it needs
`kiutils` — `pip3 install kiutils` — a pure-Python KiCad file library):

```sh
python3 hardware/xor-trial/kicad/gen_sch.py
```

The **board** generator needs KiCad's own Python (for `pcbnew`), not the system
python:

```sh
PYK=/Applications/KiCad/KiCad.app/Contents/Frameworks/Python.framework/Versions/3.9/bin/python3
"$PYK" hardware/xor-trial/kicad/gen_xor.py
```

## Check + export (kicad-cli)

```sh
CLI=/Applications/KiCad/KiCad.app/Contents/MacOS/kicad-cli
# schematic: ERC + PDF
"$CLI" sch erc xor_trial.kicad_sch                       # 0 violations
"$CLI" sch export pdf -o xor_trial_sch.pdf xor_trial.kicad_sch
# board: DRC + Gerbers + drill
"$CLI" pcb drc xor_trial.kicad_pcb                       # 0 violations, 0 unconnected
"$CLI" pcb export gerbers --no-protel-ext -o gerbers/ xor_trial.kicad_pcb
"$CLI" pcb export drill --format excellon --excellon-units mm -o gerbers/ xor_trial.kicad_pcb
( cd gerbers && zip ../xor_trial_gerbers.zip *.gbr *.gbrjob *.drl )
```

The committed schematic passes ERC clean (0 violations) and the board passes
DRC clean (0 violations, 0 unconnected).

## How the schematic is built (and why the s-expression is hand-emitted)

`gen_sch.py` lifts the full symbol definitions (R, C, LED, SW_Push, the
connector, the 74xx gate, the power ports) straight out of the installed
`.kicad_sym` libraries with `kiutils`, so no symbol geometry is hand-copied. It
then writes the modern (KiCad 8, `version 20231120`) schematic body itself —
placing each symbol with its own `(instances (project …))` block, drawing net
labels + short stubs for the signals, and dropping `+5V` / `GND` power symbols
on the rails with one `PWR_FLAG` each so ERC knows power enters at J1.

Two details are load-bearing:

- **Not the old kiutils file format.** `kiutils` writes the KiCad-6 format
  (`20211014`). KiCad 10 opens it, but its net/ERC engine does not pick up
  symbols placed in that older per-schematic `symbol_instances` style — a
  netlist export comes back with *zero* components and ERC then "passes" on an
  empty sheet (a false clean). The per-symbol `instances` block in the newer
  format is what actually registers components and nets.
- **The XOR symbol is `74xx:74LS86`, valued `74HC86`.** In KiCad `74HC86` is a
  *derived* symbol (`extends 74LS86`, identical body). A hand-flattened copy of
  a derived symbol never byte-matches KiCad's internal form, so ERC's
  `lib_symbol_mismatch` check flags it. Placing the concrete base symbol and
  carrying the real part number in the Value field avoids that with no loss of
  fidelity (same pinout, same footprint).

Everything is placed on the 1.27 mm (50 mil) connection grid so no pin lands
off-grid.

## How it's routed

- **GND** is a **bottom-layer copper pour**. Every part here is through-hole, so
  its pads penetrate the bottom layer and connect to the pour automatically — no
  GND tracks to draw.
- **VCC** runs on the top layer: up from J1, across the top through both buttons'
  top pads, with branches down to U1 pin 14 and to C1.
- The **signal** nets (`N1A`, `N1B`, `N1Y`, `NLED`) route on top where they can;
  `N1B` and `N1Y` take a short **bottom** hop (again via the THT pads, no vias) to
  reach U1's left-hand pins without crossing anything or skimming a GND pad.

## Order it

Upload **`xor_trial_gerbers.zip`** to any fab (JLCPCB / PCBWay / OSHPark — all take
this Gerber+drill set). Defaults are fine: 2-layer, 1.6 mm FR4, HASL. Then stuff it
with the [BOM in the parent README](../README.md#bill-of-materials) — all common
through-hole parts.

> This is the first board taken through **KiCad** (the rest of the machine uses the
> Eagle flow in `generators/gen_eagle.py`). It's a trial of that toolchain on a
> deliberately tiny circuit; the pcbnew-generator approach mirrors the "generators
> are canon" rule the Eagle boards follow.

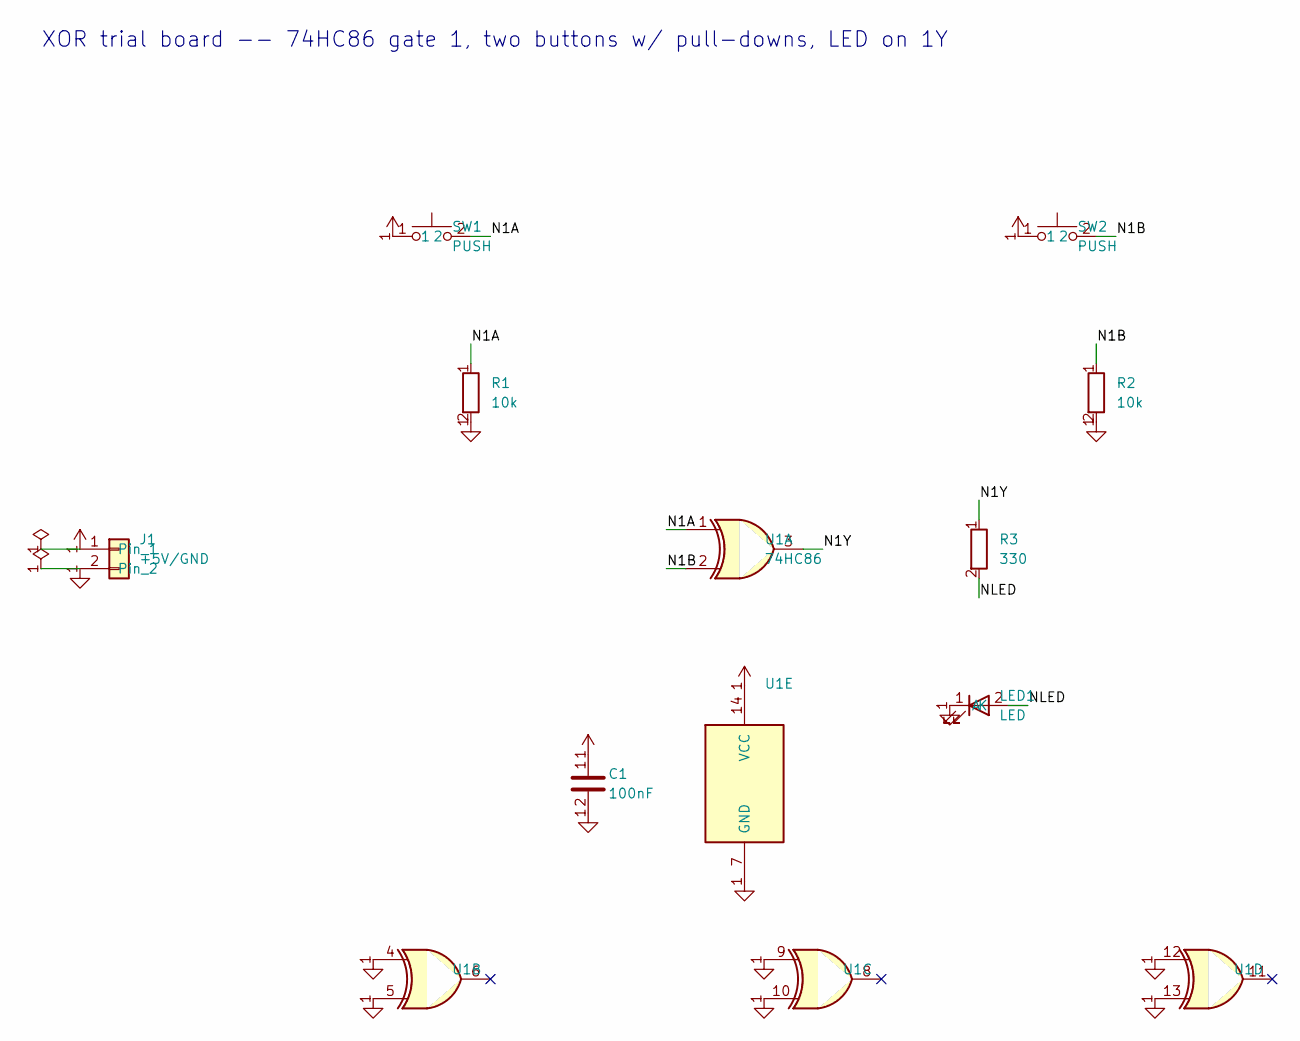
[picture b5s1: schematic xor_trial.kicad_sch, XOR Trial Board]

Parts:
C1: 100nF
J1: +5V/GND
LED1: LED
R1, R2: 10k
R3: 330
SW1, SW2: PUSH
U1: 74HC86

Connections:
GND: C1.2, J1.2, LED1.1 (K), R1.2, R2.2, U1.4, U1.5, U1.7 (GND), U1.9, U1.10, U1.12, U1.13
N1A: R1.1, SW1.2, U1.1
N1B: R2.1, SW2.2, U1.2
N1Y: R3.1, U1.3
NLED: LED1.2 (A), R3.2
VCC: C1.1, J1.1, SW1.1, SW2.1, U1.14 (VCC)

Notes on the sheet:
XOR trial board -- 74HC86 gate 1, two buttons w/ pull-downs, LED on 1Y

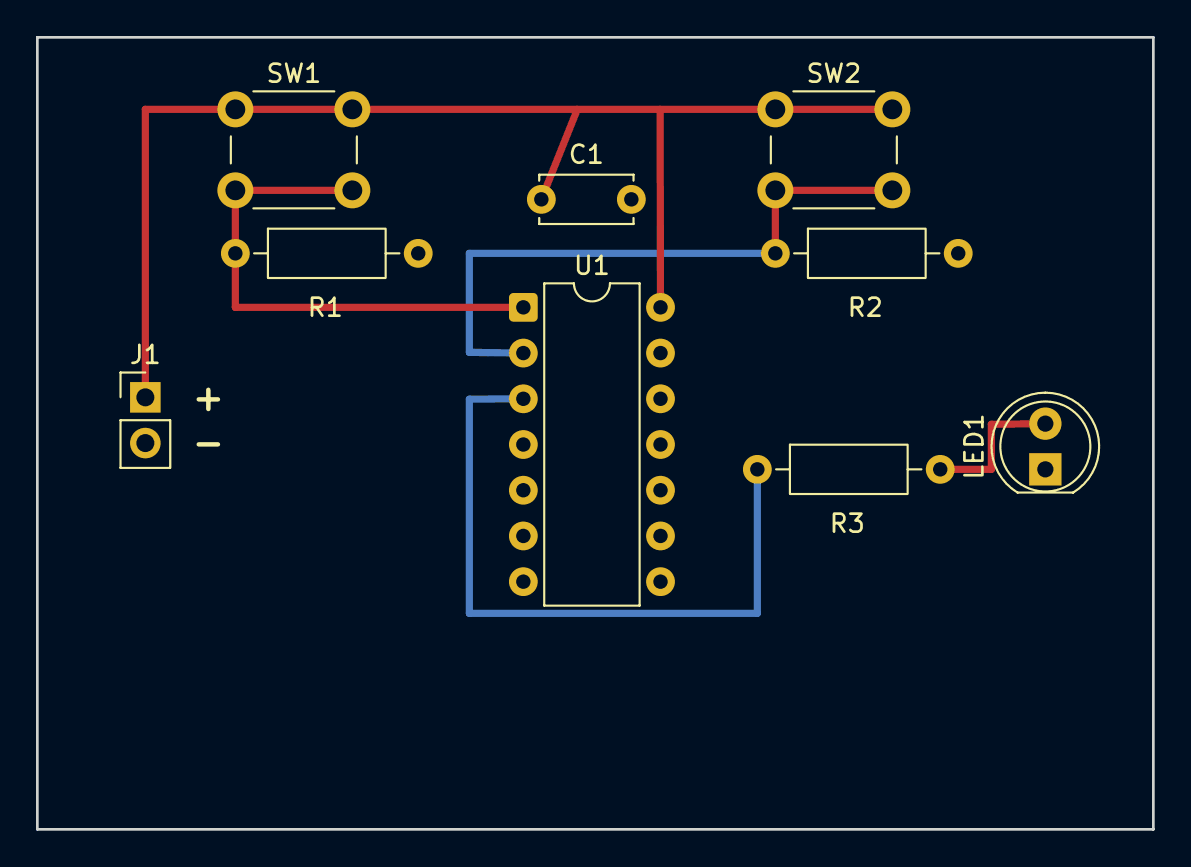
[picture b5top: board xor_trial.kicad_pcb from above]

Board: 2 copper layers, 62.0 x 44.0 mm, 9 parts (0 on the bottom side), 6 nets.

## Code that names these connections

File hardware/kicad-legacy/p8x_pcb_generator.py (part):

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        if n==11: return "RES_N"
        if 12<=n<=15: return "DOE%d"%(n-12)
        if 16<=n<=19: return "DLD%d"%(n-16)
        return {20:"PSEL0",21:"PSEL1",22:"PINC",23:"PDEC",24:"CLK",25:"CLKB",26:"LDF"}.get(n,"SPARE%d"%(n-27))
    if r=="C":
        if 3<=n<=18: return "A%d"%(n-3)
        if 19<=n<=22: return "ALUS%d"%(n-19)
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    [bp.pad("1",0,0,1.6,0.8,"CLK"),bp.pad("2",10.16,0,1.6,0.8,"CLK_T")])
bp.footprint("CT1","C_DISC",218.44,piny(24),
    [bp.pad("1",0,0,1.8,0.9,"CLK_T"),bp.pad("2",0,5.08,1.8,0.9,"GND")])
bp.seg(EXTCLK+10.16,piny(24),218.44,piny(24),"F.Cu","CLK_T")
bp.footprint("RT2","R_AXIAL",EXTCLK,piny(25),
    [bp.pad("1",0,0,1.6,0.8,"CLKB"),bp.pad("2",10.16,0,1.6,0.8,"CLKB_T")])
bp.footprint("CT2","C_DISC",220.98,piny(25),
    [bp.pad("1",0,0,1.8,0.9,"CLKB_T"),bp.pad("2",0,5.08,1.8,0.9,"GND")])
bp.seg(EXTCLK+10.16,piny(25),220.98,piny(25),"F.Cu","CLKB_T")
# power entry + bulk + per-slot decoupling + LED
bp.footprint("J11","TB4",5.08,30.48,
    [bp.pad(str(k+1),0,5.08*k,3.0,1.3,"VCC" if k<2 else "GND") for k in range(4)])
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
